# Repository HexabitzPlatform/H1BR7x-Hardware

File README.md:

# H1BR7x-Hardware
Hexabitz USB-C Mass Storage Device Module Hardware Design

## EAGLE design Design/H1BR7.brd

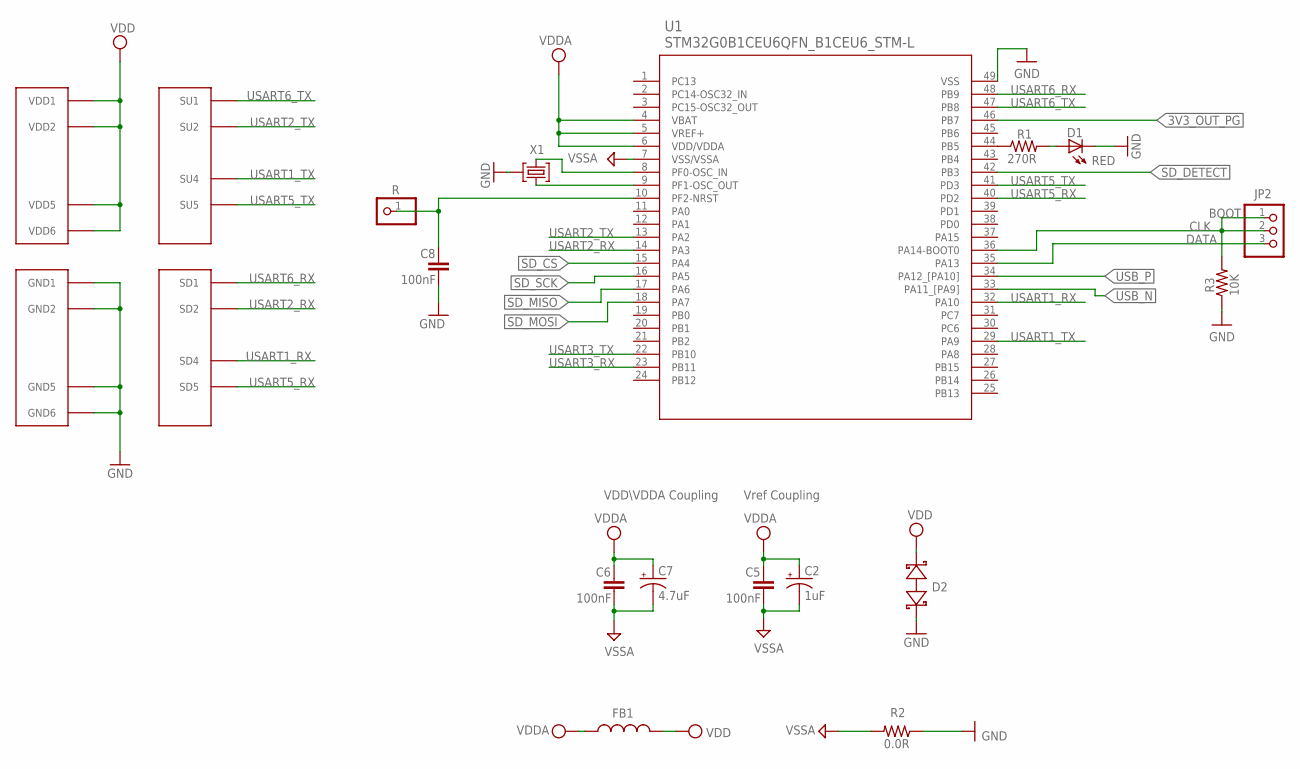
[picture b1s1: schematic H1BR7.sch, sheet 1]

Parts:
C2: 1uF; C-0805-POL
C5, C6, C8: 100nF; C-0603
C7: 4.7uF; C-0805-POL
D1: RED; VLMS1300-GS08; MPN VLMS1300-GS08
D2: BOURNS_CDSOD323-T03SCBOURNS_CDSOD323-T03SC_0_0; BOURNS_CDSOD323-T03SC_0
FB1: FB-TDK_MMZ1608Y300B; MPN MMZ1608Y300B
JP2: PINHD-1X3; 1X03
P1: HEXABIT_HEXABIT_?_NO_P3_P6_P9_P10; HEXABIT_?_NO_P3_P6_P9_P10
R: R; 1X01
R1: 270R; R-0603
R2: 0.0R; R-0603; MPN RC0603JR-070RL
R3: 10K; R-0603
TRIMBLE-LOGO1: HEXA-LOGO
U1: STM32G0B1CEU6QFN_B1CEU6_STM-L; QFN_B1CEU6_STM-L
X1: XTALL_CSTCE8M00G52

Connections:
3V3_OUT_PG: U1.46 (PB7); also elsewhere on the board
CLK: JP2.1, JP2.2, R3.2, U1.36 (PA14-BOOT0)
DATA: JP2.3, U1.35 (PA13)
GND: C8.2, D1.C, D2.1 (A), P1.PAD_PD7 (GND1), P1.PAD_PD8 (GND2), P1.PAD_PD11 (GND5), P1.PAD_PD12 (GND6), R2.1, R3.1, U1.49 (VSS), X1.P$2 (2); also elsewhere on the board
unnamed: R1.1, U1.44 (PB5)
unnamed: D1.A, R1.2
unnamed: C8.1, R.1, U1.10 (PF2-NRST)
unnamed: U1.9 (PF1-OSC_OUT), X1.P$1 (1)
unnamed: U1.8 (PF0-OSC_IN), X1.P$3 (3)
SD_CS: U1.15 (PA4); also elsewhere on the board
SD_DETECT: U1.42 (PB3); also elsewhere on the board
SD_MISO: U1.17 (PA6); also elsewhere on the board
SD_MOSI: U1.18 (PA7); also elsewhere on the board
SD_SCK: U1.16 (PA5); also elsewhere on the board
USART1_RX: P1.PAD_PD4 (SD4), U1.32 (PA10)
USART1_TX: P1.PAD_PU4 (SU4), U1.29 (PA9)
USART2_RX: P1.PAD_PD2 (SD2), U1.14 (PA3)
USART2_TX: P1.PAD_PU2 (SU2), U1.13 (PA2)
USART3_RX: U1.23 (PB11)
USART3_TX: U1.22 (PB10)
USART5_RX: P1.PAD_PD5 (SD5), U1.40 (PD2)
USART5_TX: P1.PAD_PU5 (SU5), U1.41 (PD3)
USART6_RX: P1.PAD_PD1 (SD1), U1.48 (PB9)
USART6_TX: P1.PAD_PU1 (SU1), U1.47 (PB8)
USB_N: U1.33 (PA11_[PA9]); also elsewhere on the board
USB_P: U1.34 (PA12_[PA10]); also elsewhere on the board
VDD: D2.2 (C), FB1.2, P1.PAD_PU7 (VDD1), P1.PAD_PU8 (VDD2), P1.PAD_PU11 (VDD5), P1.PAD_PU12 (VDD6); also elsewhere on the board
VDDA: C2.1 (+), C5.1, C6.1, C7.1 (+), FB1.1, U1.4 (VBAT), U1.5 (VREF+), U1.6 (VDD/VDDA)
VSSA: C2.2 (-), C5.2, C6.2, C7.2 (-), R2.2, U1.7 (VSS/VSSA)

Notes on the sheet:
Vref Coupling
VDD\VDDA Coupling
BOOT

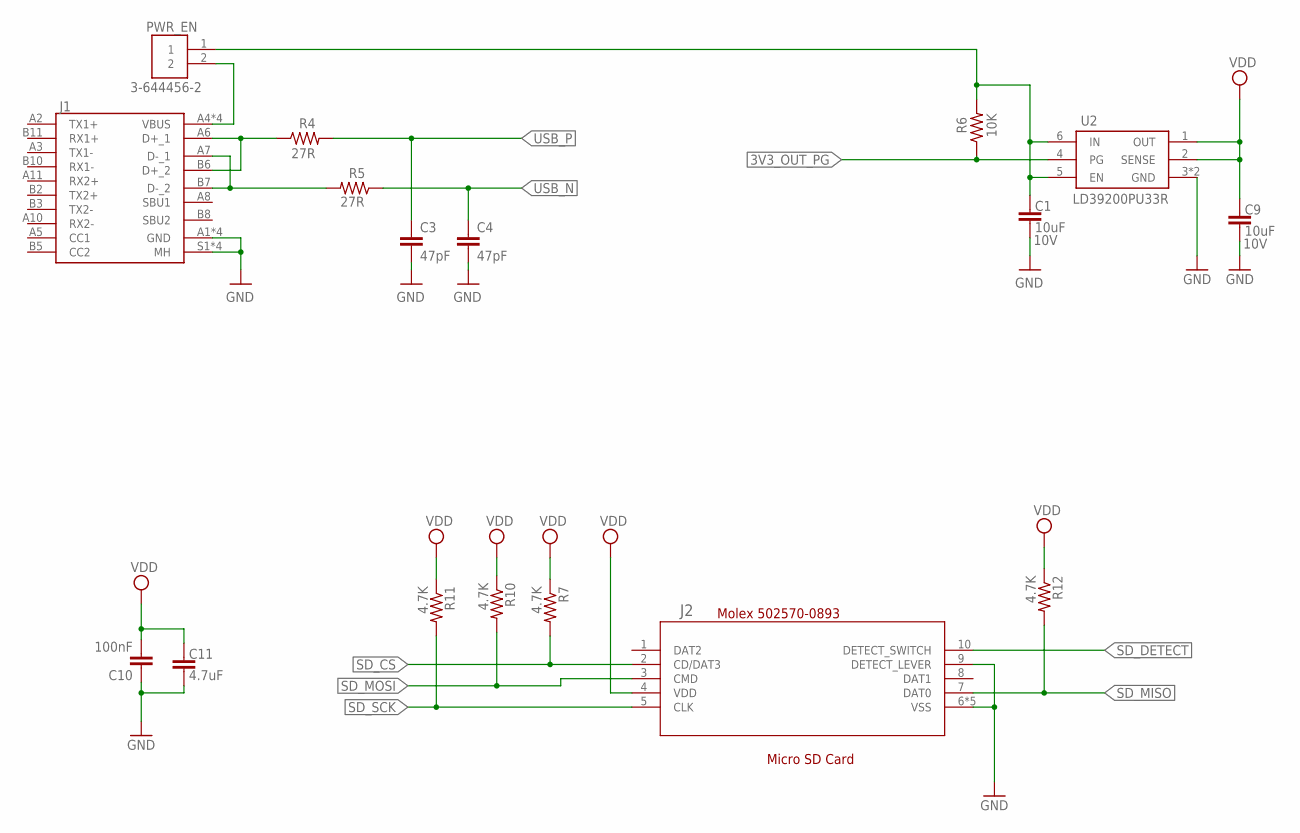
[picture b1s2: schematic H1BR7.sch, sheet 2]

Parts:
C1, C9: 10uF; C-0805; VOLTAGE_RATING 10V; MPN GRM187R61A226ME15
C3, C4: 47pF; C-0603
C10: 100nF; C-0603; TOLERANCE 10%; VOLTAGE_RATING 16.0 V; MPN '0603YC104K4T2A
C11: 4.7uF; C-0805; VOLTAGE_RATING 10V; MPN GRM187R61A226ME15
J1: 12401610E4#2A12401610E42A; AMPHENOL_12401610E4_2A
J2: 5025700893502570-0893_MOL; 502570-0893_MOL
PWR_EN: 3-644456-2; TE_3-644456-2
R4, R5: 27R; R-0603; TOLERANCE 1%
R6: 10K; R-0603; TOLERANCE 1%
R7, R10, R11, R12: 4.7K; R-0603; TOLERANCE 5%; MPN RC0603JR-074K7L
U2: LD39200PU33R; SON95P300X300X100-7N

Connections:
3V3_OUT_PG: R6.1, U2.4 (PG); also elsewhere on the board
D_N: J1.A7 (D-_1), J1.B7 (D-_2), R5.2
D_P: J1.A6 (D+_1), J1.B6 (D+_2), R4.1
GND: C1.1, C3.2, C4.2, C9.1, C10.1, C11.1, J1.A1 (GND), J1.A12 (GND), J1.B1 (GND), J1.B12 (GND), J1.S1 (MH), J1.S2 (MH), J1.S3 (MH), J1.S4 (MH), J2.6 (VSS), J2.9 (DETECT_LEVER), J2.11 (VSS), J2.12 (VSS), J2.13 (VSS), J2.14 (VSS), U2.3 (GND), U2.7 (GND); also elsewhere on the board
unnamed: C1.2, PWR_EN.1, R6.2, U2.5 (EN), U2.6 (IN)
unnamed: J1.A4 (VBUS), J1.A9 (VBUS), J1.B4 (VBUS), J1.B9 (VBUS), PWR_EN.2
SD_CS: J2.2 (CD/DAT3), R7.2; also elsewhere on the board
SD_DETECT: J2.10 (DETECT_SWITCH); also elsewhere on the board
SD_MISO: J2.7 (DAT0), R12.2; also elsewhere on the board
SD_MOSI: J2.3 (CMD), R10.2; also elsewhere on the board
SD_SCK: J2.5 (CLK), R11.2; also elsewhere on the board
USB_N: C4.1, R5.1; also elsewhere on the board
USB_P: C3.1, R4.2; also elsewhere on the board
VDD: C9.2, C10.2, C11.2, J2.4 (VDD), R7.1, R10.1, R11.1, R12.1, U2.1 (OUT), U2.2 (SENSE); also elsewhere on the board

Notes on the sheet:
Micro SD Card
Molex 502570-0893

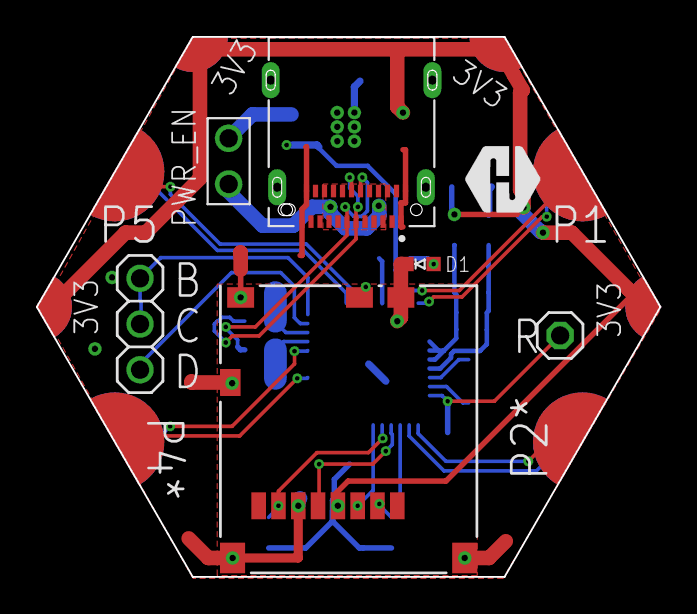
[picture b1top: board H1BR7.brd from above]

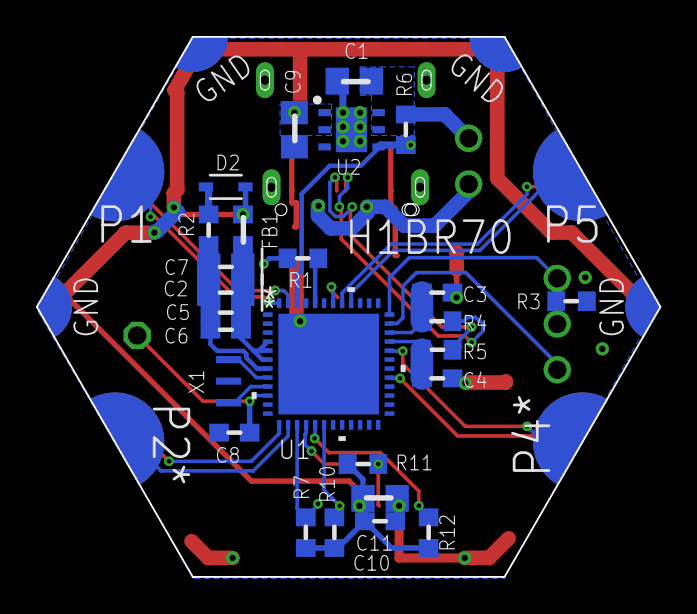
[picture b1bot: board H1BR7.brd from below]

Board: 2 copper layers, 34.6 x 30.0 mm, 34 parts (26 on the bottom side), 31 nets.

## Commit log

2024-12-27 -The final design, all done.

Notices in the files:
parts and their libraries:
COPYRIGHT: Copyright (C) 2021 Ultra Librarian. All rights reserved.
COPYRIGHT: Copyright (C) 2022 Ultra Librarian. All rights reserved.
